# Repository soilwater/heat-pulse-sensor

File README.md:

# heat-pulse

Information, datasets, and digital twins for heat-pulse sensors that measure soil thermal properties.

**Digital twin:** an interactive simulation of the HP-SDI12-NANO sensor running in real Kansas soils, published from [`docs/`](docs/). Open `docs/index.html` locally in Chrome or Edge; no installation is needed. **Guided tour** in its header steps through one measurement part by part.

## Repository layout

| Folder | Contents |
|---|---|
| [`docs/`](docs/) | The digital-twin website (static HTML, CSS and JavaScript; served as-is) |
| [`digital-twin/`](digital-twin/) | How the twin works, its data builders and tests, and the soil and heater analyses ([KANSAS_SOIL.md](digital-twin/KANSAS_SOIL.md)) |
| [`flat-nano/`](flat-nano/) | Main sensor board, HP-SDI12-NANO: KiCad sources, release checks and manufacturing files |
| [`hat/`](hat/) | Secondary design: a heat-pulse hat for the Arduino Nano R4 |
| [`reference/`](reference/) | Lab data used by the twin (Kansas Mesonet KD2 Pro workbook, logger record). Vendor manuals are kept locally, not in the repository |

## Working on the twin

```powershell
node digital-twin/sensor-model.test.js
node digital-twin/sensor-routes.test.js
node digital-twin/kansas-soil.test.js
node digital-twin/kansas-soil-build.js                          # rebuild docs/kansas-soil-data.js
& 'D:/KiCAD/bin/python.exe' 'digital-twin/export_board.py'      # rebuild docs/board-data.js from the board
```

Board release steps are in each board's README.

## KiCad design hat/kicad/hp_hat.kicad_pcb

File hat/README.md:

# Compact Nano R4 heat-pulse hat

Current design: **HP-HAT**, four layers, 0.8 mm thick. The 43.18 × 17.78 mm body is exactly the Arduino Nano R4 outline and pin layout, with parts on both faces.

- [Assembly dimensions, selected headers and drawing](mechanical/ASSEMBLY.md)
- [Design, operation and manufacturing files](fab/README_HAT.md)
- [JLCPCB order settings](fab/ORDER_SETTINGS.md)
- [Release checks and file hashes](fab/RELEASE_MANIFEST.txt)

The `flat-nano` version is the reference for the needles and shared parts; its files are only read. The Nano and hat are soldered face inward with a 4.00 mm gap. The potted body target is 10.5 mm thick, which the nominal 10.49 mm stack meets only with the full 1 mm cover per face; verify the fit on the first assembly.

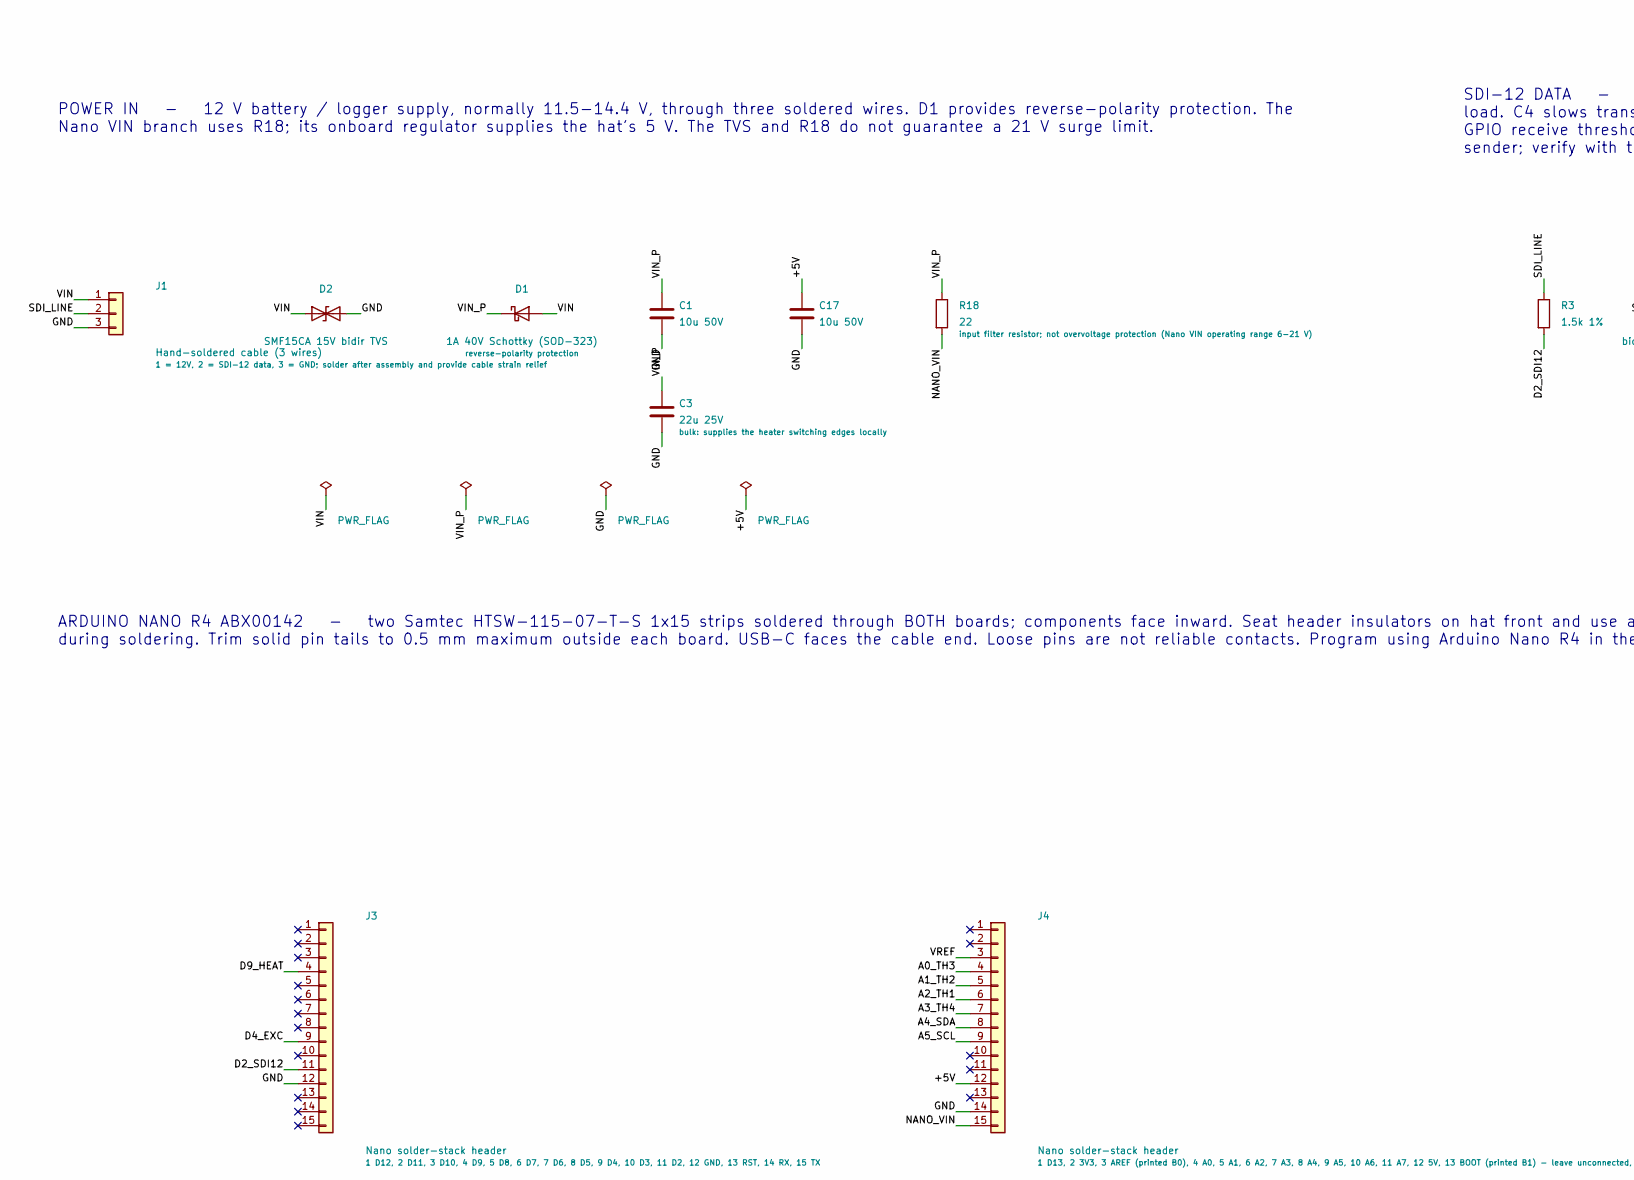
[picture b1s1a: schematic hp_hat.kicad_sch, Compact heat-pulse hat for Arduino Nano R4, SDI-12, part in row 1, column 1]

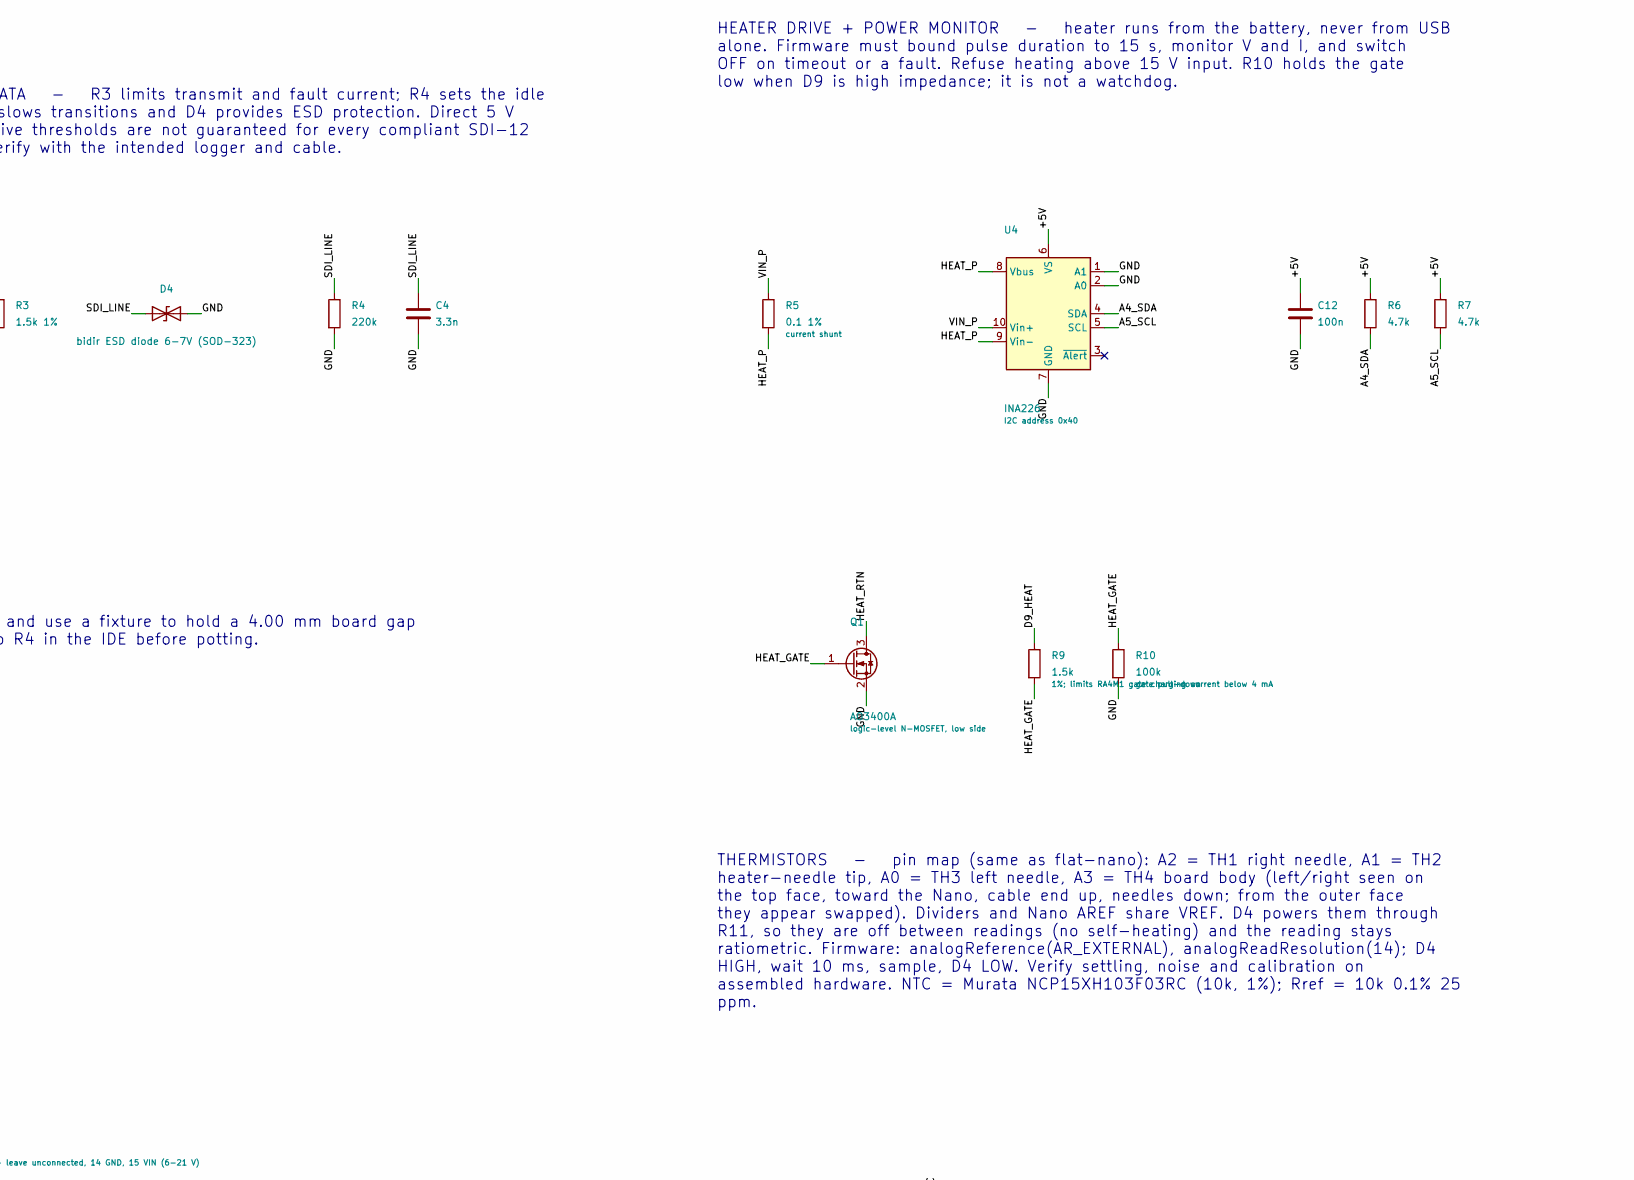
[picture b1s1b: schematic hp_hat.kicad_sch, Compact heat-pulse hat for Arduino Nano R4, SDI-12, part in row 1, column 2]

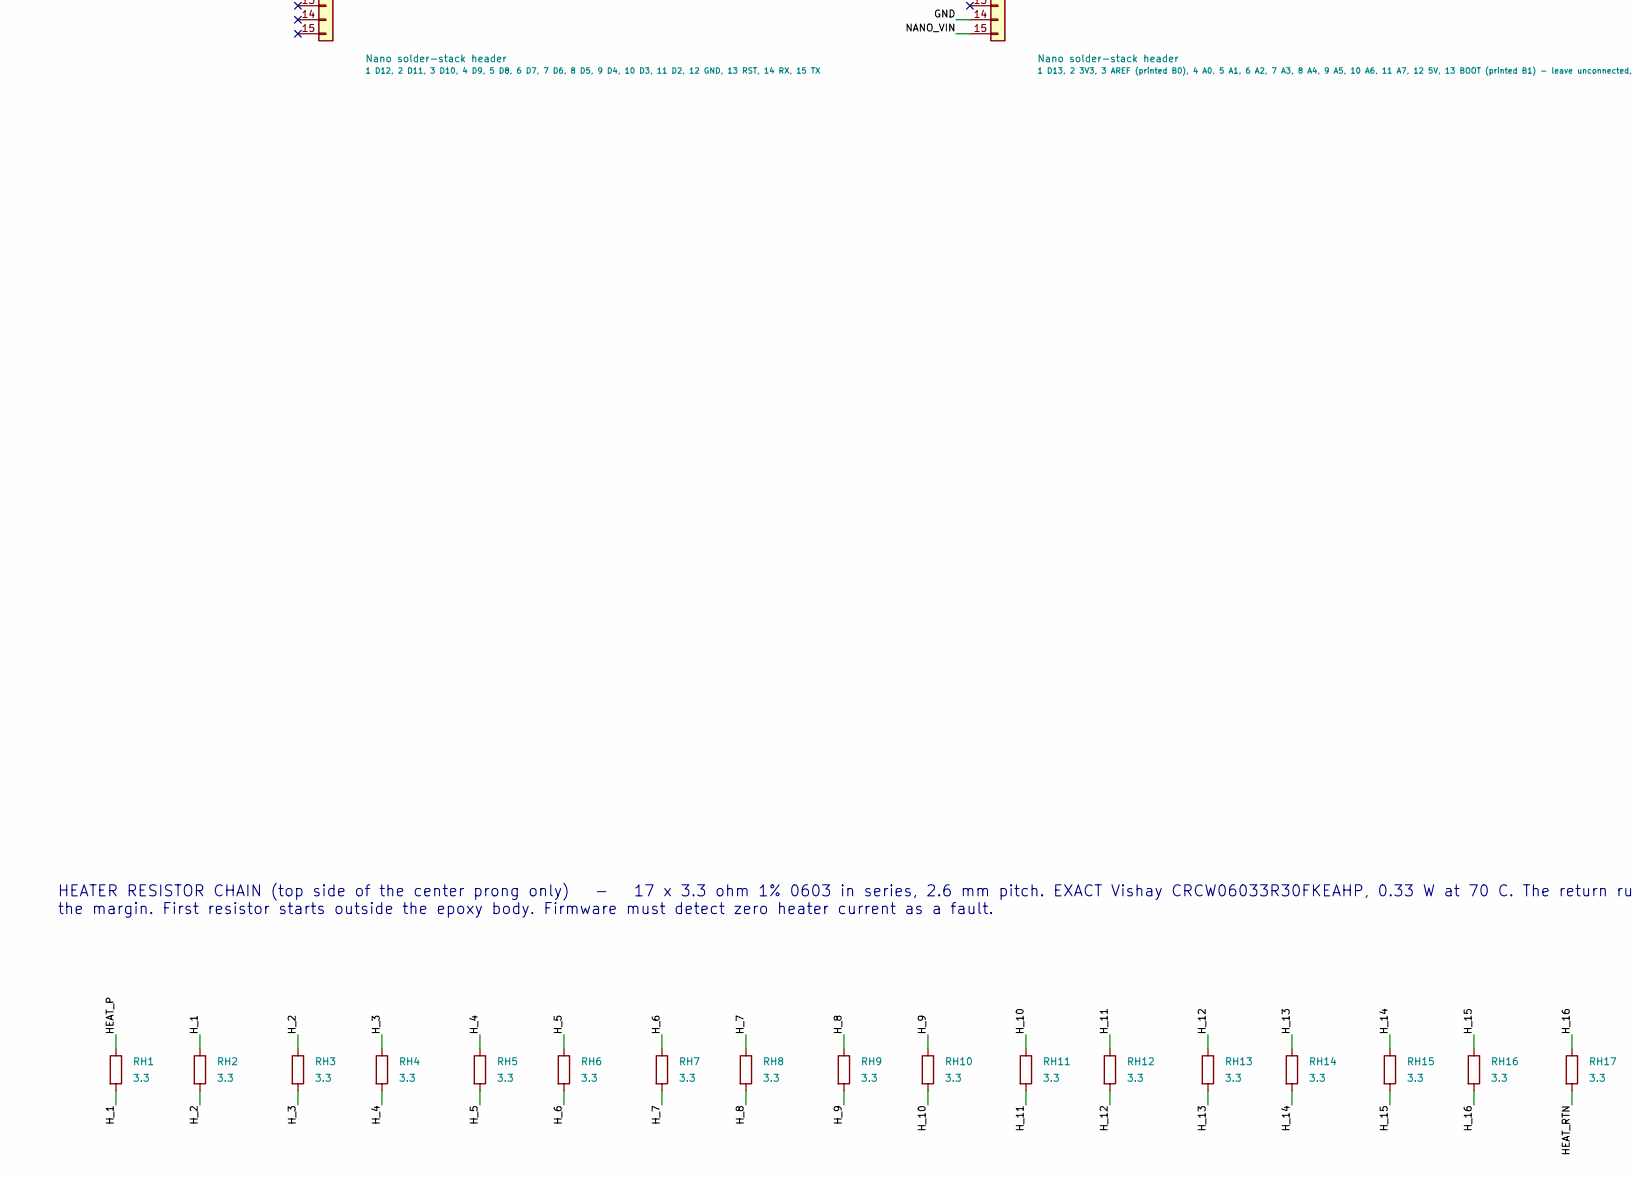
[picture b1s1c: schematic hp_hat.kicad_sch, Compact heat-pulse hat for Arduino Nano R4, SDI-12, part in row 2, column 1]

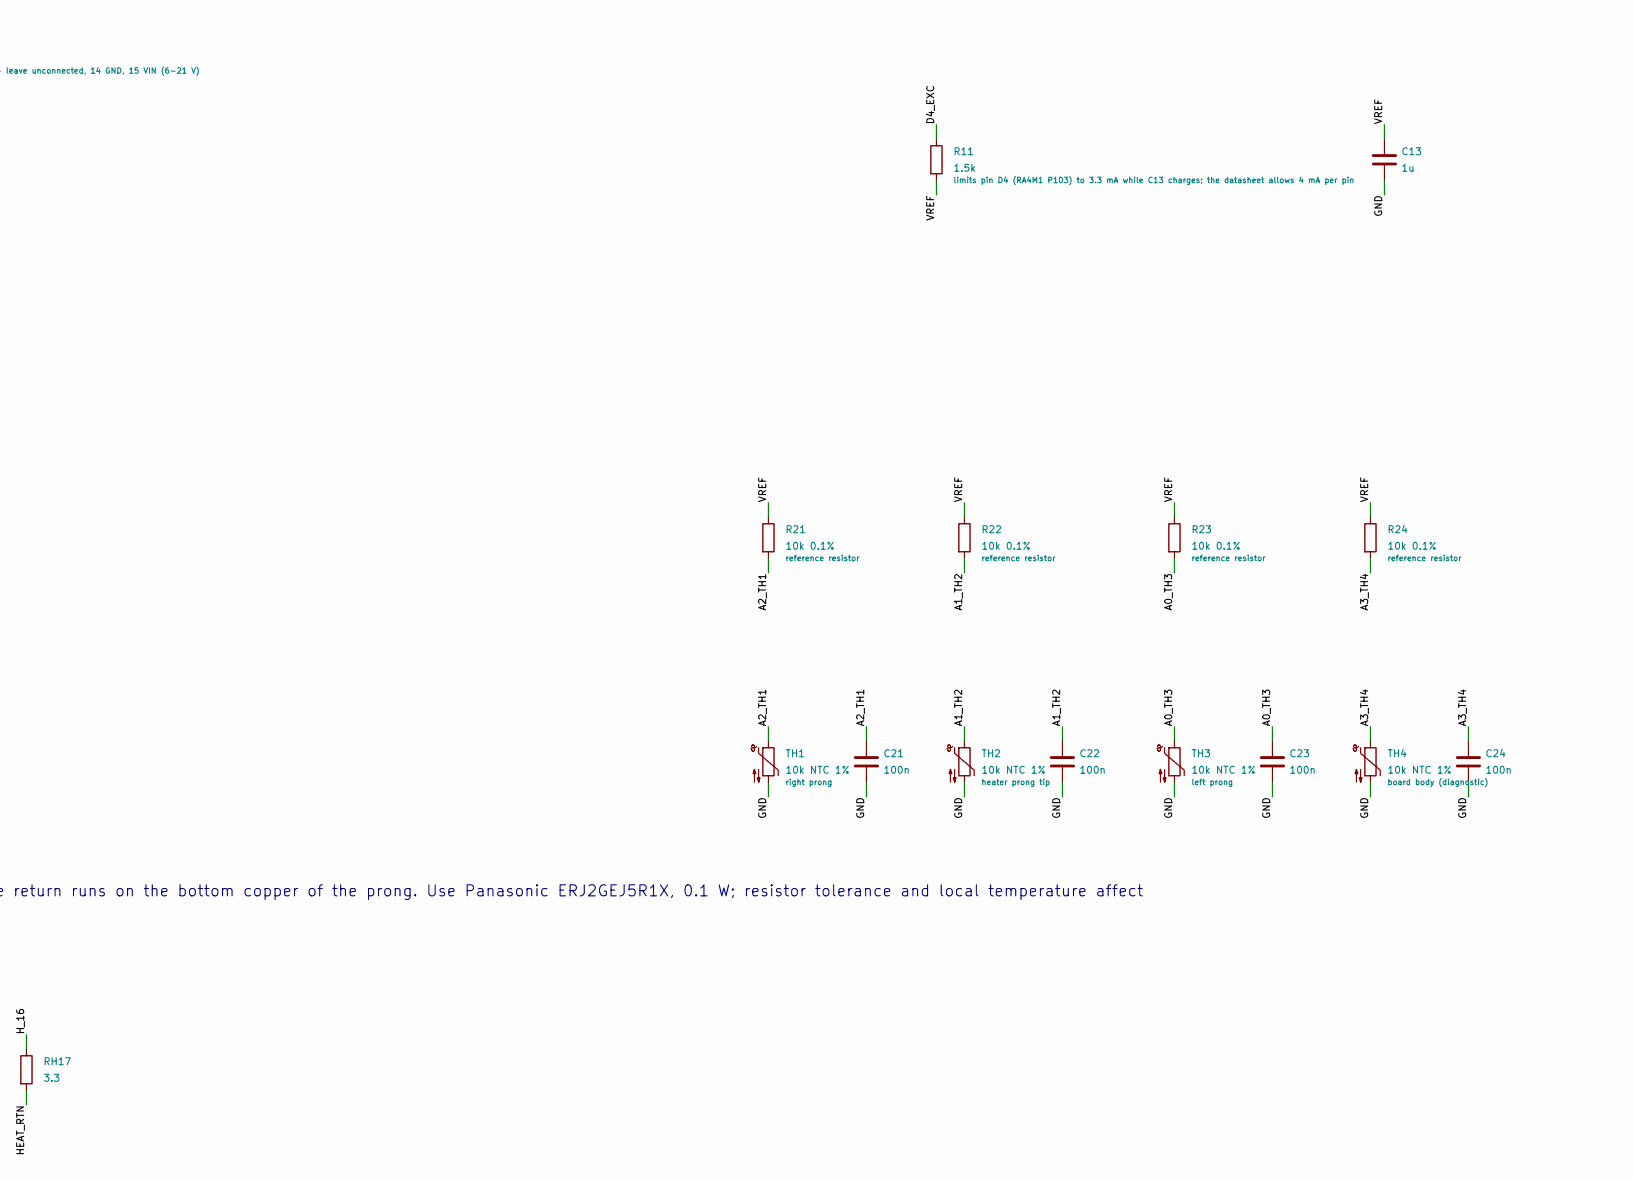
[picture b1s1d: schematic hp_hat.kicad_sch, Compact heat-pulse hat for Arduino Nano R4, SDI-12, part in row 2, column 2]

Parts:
C1, C17: 10u 50V; C_0805_2012Metric
C3: 22u 25V; C_1206_3216Metric
C4: 3.3n; C_0402_1005Metric
C12, C21, C22, C23, C24: 100n; C_0402_1005Metric
C13: 1u; C_0402_1005Metric
D1: 1A 40V Schottky (SOD-323); D_SOD-323
D2: SMF15CA 15V bidir TVS; D_SOD-123F
D4: bidir ESD diode 6-7V (SOD-323); D_SOD-323
J1: Hand-soldered cable (3 wires); CableSolder_1x03
J3, J4: Nano solder-stack header; Nano_SolderStack_1x15
Q1: AO3400A; SOT-23
R3: 1.5k 1%; R_0603_1608Metric
R4: 220k; R_0402_1005Metric
R5: 0.1 1%; R_0805_2012Metric
R6, R7: 4.7k; R_0402_1005Metric
R9, R11: 1.5k; R_0402_1005Metric
R10: 100k; R_0402_1005Metric
R18: 22; R_0603_1608Metric
R21, R22, R23, R24: 10k 0.1%; R_0603_1608Metric
RH1, RH2, RH3, RH4, RH5, RH6, RH7, RH8, RH9, RH10, RH11, RH12, RH13, RH14, RH15, RH16, RH17: 3.3; R_0603_Vishay_HP
TH1, TH2, TH3, TH4: 10k NTC 1%; R_0402_1005Metric
U4: INA226; MSOP-10_3x3mm_P0.5mm

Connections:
+5V: C12.1, C17.1, J4.12, R6.1, R7.1, U4.6 (VS)
A0_TH3: C23.1, J4.4, R23.2, TH3.1
A1_TH2: C22.1, J4.5, R22.2, TH2.1
A2_TH1: C21.1, J4.6, R21.2, TH1.1
A3_TH4: C24.1, J4.7, R24.2, TH4.1
A4_SDA: J4.8, R6.2, U4.4 (SDA)
A5_SCL: J4.9, R7.2, U4.5 (SCL)
D2_SDI12: J3.11, R3.2
D4_EXC: J3.9, R11.1
D9_HEAT: J3.4, R9.1
GND: C1.2, C3.2, C4.2, C12.2, C13.2, C17.2, C21.2, C22.2, C23.2, C24.2, D2.2 (A2), D4.2 (A2), J1.3, J3.12, J4.14, Q1.2 (S), R4.2, R10.2, TH1.2, TH2.2, TH3.2, TH4.2, U4.1 (A1), U4.2 (A0), U4.7 (GND)
HEAT_GATE: Q1.1 (G), R9.2, R10.1
HEAT_P: R5.2, RH1.1, U4.8 (Vbus), U4.9 (Vin-)
HEAT_RTN: Q1.3 (D), RH17.2
H_1: RH1.2, RH2.1
H_2: RH2.2, RH3.1
H_3: RH3.2, RH4.1
H_4: RH4.2, RH5.1
H_5: RH5.2, RH6.1
H_6: RH6.2, RH7.1
H_7: RH7.2, RH8.1
H_8: RH8.2, RH9.1
H_9: RH9.2, RH10.1
H_10: RH10.2, RH11.1
H_11: RH11.2, RH12.1
H_12: RH12.2, RH13.1
H_13: RH13.2, RH14.1
H_14: RH14.2, RH15.1
H_15: RH15.2, RH16.1
H_16: RH16.2, RH17.1
NANO_VIN: J4.15, R18.2
SDI_LINE: C4.1, D4.1 (A1), J1.2, R3.1, R4.1
VIN: D1.2 (A), D2.1 (A1), J1.1
VIN_P: C1.1, C3.1, D1.1 (K), R5.1, R18.1, U4.10 (Vin+)
VREF: C13.1, J4.3, R11.2, R21.1, R22.1, R23.1, R24.1

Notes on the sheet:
POWER IN - 12 V battery / logger supply, normally 11.5-14.4 V, through three soldered wires. D1 provides reverse-polarity protection. The Nano VIN branch uses R18; its onboard regulator supplies the hat's 5 V. The TVS and R18 do not guarantee a 21 V surge limit.
SDI-12 DATA - R3 limits transmit and fault current; R4 sets the idle load. C4 slows transitions and D4 provides ESD protection. Direct 5 V GPIO receive thresholds are not guaranteed for every compliant SDI-12 sender; verify with the intended logger and cable.
ARDUINO NANO R4 ABX00142 - two Samtec HTSW-115-07-T-S 1x15 strips soldered through BOTH boards; components face inward. Seat header insulators on hat front and use a fixture to hold a 4.00 mm board gap during soldering. Trim solid pin tails to 0.5 mm maximum outside each board. USB-C faces the cabl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
HEATER DRIVE + POWER MONITOR - heater runs from the battery, never from USB alone. Firmware must bound pulse duration to 15 s, monitor V and I, and switch OFF on timeout or a fault. Refuse heating above 15 V input. R10 holds the gate low when D9 is high impedance; it is not a watchdog.
HEATER RESISTOR CHAIN (top side of the center prong only) - 17 x 3.3 ohm 1% 0603 in series, 2.6 mm pitch. EXACT Vishay CRCW06033R30FKEAHP, 0.33 W at 70 C. The return runs on the bottom copper of the prong. Use Panasonic ERJ2GEJ5R1X, 0.1 W; resistor tolerance and local temperature affect the margin.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
THERMISTORS - pin map (same as flat-nano): A2 = TH1 right needle, A1 = TH2 heater-needle tip, A0 = TH3 left needle, A3 = TH4 board body (left/right seen on the top face, toward the Nano, cable end up, needles down; from the outer face they appear swapped). Dividers and Nano AREF share VREF. D4 powe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

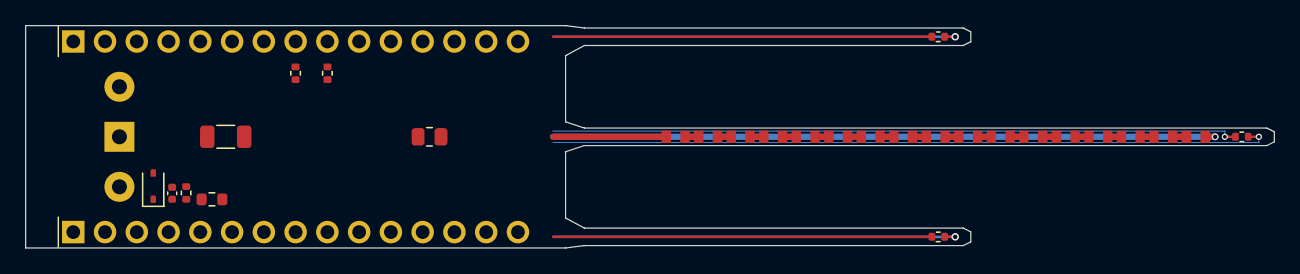
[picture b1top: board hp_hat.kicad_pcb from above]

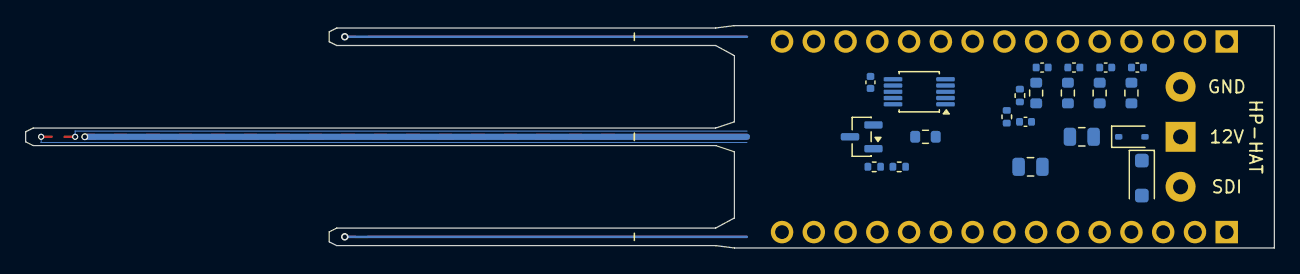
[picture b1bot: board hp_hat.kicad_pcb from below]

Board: 4 copper layers, 99.9 x 17.8 mm, 52 parts (21 on the bottom side), 35 nets.

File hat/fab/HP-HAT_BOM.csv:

Comment,Designator,Footprint,LCSC Part #,Manufacturer Part Number,Qty,Description
10u 50V,"C1,C17",C_0805_2012Metric,C440198,GRM21BR61H106KE43L,2,MLCC 10 uF 50 V X5R 0805 (VIN input C1 and +5 V output C17)
22u 25V,C3,C_1206_3216Metric,C12891,CL31A226KAHNNNE,1,MLCC 22 uF 25 V X5R 1206 (bulk input capacitor)
3.3n,C4,C_0402_1005Metric,C26404,CL05B332KB5NNNC,1,MLCC 3.3 nF 50 V X7R 0402
100n,"C12,C21,C22,C23,C24",C_0402_1005Metric,C307331,CL05B104KB54PNC,5,MLCC 100 nF 50 V X7R 0402
1u,C13,C_0402_1005Metric,C52923,CL05A105KA5NQNC,1,MLCC 1 uF 25 V X5R 0402
1A 40V Schottky (SOD-323),D1,D_SOD-323,C191023,1N5819WS,1,"Schottky 1 A 40 V, SOD-323"
SMF15CA 15V bidir TVS,D2,D_SOD-123F,C19077510,SMF15CA,1,"TVS 15 V standoff, bidirectional, SOD-123FL (clamp about 24 V)"
bidir ESD diode 6-7V (SOD-323),D4,D_SOD-323,C19224,"PESD5V0S1BA,115",1,"ESD diode bidirectional 5 V, SOD-323"
AO3400A,Q1,SOT-23,C20917,AO3400A,1,"N-MOSFET 30 V logic level, SOT-23"
1.5k 1%,R3,R_0603_1608Metric,C22843,0603WAF1501T5E,1,Resistor 1.5 k 1 % 0603 (SDI-12 transmit resistance)
220k,R4,R_0402_1005Metric,C25767,0402WGF2203TCE,1,Resistor 220 k 1 % 0402
0.1 1%,R5,R_0805_2012Metric,C2094615,WSL0805R1000FEA,1,"Current-sense resistor 0.1 ohm 1 %, 0805 - no substitutes"
4.7k,"R6,R7",R_0402_1005Metric,C25900,0402WGF4701TCE,2,Resistor 4.7 k 1 % 0402
1.5k,"R9,R11",R_0402_1005Metric,C25867,0402WGF1501TCE,2,"Resistor 1.5 k ohm 1%, 0402 (R9 gate drive, R11 thermistor excitation)"
100k,R10,R_0402_1005Metric,C25741,0402WGF1003TCE,1,Resistor 100 k 1 % 0402
22,R18,R_0603_1608Metric,C23345,0603WAF220JT5E,1,Resistor 22 ohm 1 % 0603
10k 0.1%,"R21,R22,R23,R24",R_0603_1608Metric,C54973934,CRF0603Q103BN,4,"Resistor 10 k 0.1 % 25 ppm, 0603 - no substitutes"
3.3,"RH1,RH2,RH3,RH4,RH5,RH6,RH7,RH8,RH9,RH10,RH11,RH12,RH13,RH14,RH15,RH16,RH17",R_0603_Vishay_HP,C313752,CRCW06033R30FKEAHP,17,"HEATER: Vishay high-power 0603 3.3 ohm 1%, 0.33 W at 70 C, derates above 70 C. Exact CRCW-HP part required; no ordinary 0.1 W/0.125 W substitutes"
10k NTC 1%,"TH1,TH2,TH3,TH4",R_0402_1005Metric,C77131,NCP15XH103F03RC,4,"NTC thermistor 10 k 1 % B3380, 0402 - no substitutes"
INA226,U4,MSOP-10_3x3mm_P0.5mm,C49851,INA226AIDGSR,1,"TI INA226 power monitor, VSSOP-10"
